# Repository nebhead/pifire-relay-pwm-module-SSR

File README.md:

# PiFire Solid State Relay (SSR) Module PCB (v1.0.1) KiCad Files

## What is this? 

This PCB is designed to support SSR relays for controlling incoming Power(L) to the Igniter and Auger.  This board also has circuitry to support a 12V PWM fan.  This board uses compact solid state relays that are able to handle high power. This is an alternative to using an off the shelf relay module which simplifies the wiring and even allows you to use the OEM harness.  

The design intent for this board was to make a DIY accessible PCB that can be more easily put together by the maker/enthusiast of almost any skill level.  Full size components are used in most cases and most (if not all) parts should be readily available to order online.  See the [Interactive BOM](#interactive-bom) for more details about the parts used and links to order.

### Important Notes

This PCB is intended to be used with the 4.0.x PCB design ([linked below](#links-to-the-pcbs-in-this-family-of-pifire-boards)) in conjunction with v1.8.x or later of the PiFire software.

The G3MB Relays and the PSMN MOSFET footprints have been left out of this release because they were sourced from SnapMagic (for free), but are not licensed for re-distribution.  If you plan to edit this board, you may need to source those files from SnapMagic directly and add them to this project.  

### What is PiFire? 

PiFire is a SBC based Pellet Smoker Controller.  More details can be found [here](https://nebhead.github.io/PiFire) or [at the GitHub repo](https://github.com/nebhead/pifire). 

## What's in this Repository?

### KiCad Project Files 
In this repository you will find the latest KiCad design files for the  PCB.  Simply load the project file (.kicad_pro) into the KiCad software and you should be able to edit as needed.  Or if you just want to get this board made, jump to the production section below.

### Interactive BOM

There is an interactive BOM located in the [/bom](bom/) folder which details the parts and provides some pin information as well.  Use this to gather the components you may need to build this board out and refer back to it for placement help.    

[BOM + Pin Info](https://nebhead.github.io/pifire-relay-pwm-module-SSR)

_This is a standalone HTML file that was autogenerated by the excellent plugin for KiCad. See the plugin here: [https://github.com/openscopeproject/InteractiveHtmlBom](https://github.com/openscopeproject/InteractiveHtmlBom)_

### PDF of the Schematic

Preview the schematic in PDF format here: [Schematic](schematic.pdf)

### PWM Fan Pinout

The PWM fan pinout is using a standard 4-pin fan connector.  It's recommended to source the headers with retaining clip to ensure that the fan doesn't easily come unplugged.  JST headers can be used as well. 

### JLCPCB Production Files

If you wish to get these PCBs made by JLCPCB, the production files are provided in the `/production` folder.  For convenience, the file `production.zip` can simply be uploaded to JLCPCB to make it super easy to order boards.

Drop the zip file onto the order page, wait for it to upload then simply continue to order the board.  Optionally, select different board color, PCB quantity, surface finish, etc.  Most of the default settings should be sufficient. 

### Links to the PCBs in this family of PiFire Boards

This PCB is part of a family of PCBs that can be used together to create  a full PiFire system.  Generally speaking you need the Main Module/Board, a Relay Control Board and a Probe Device board to have a basic PiFire system.  

**Main Module/Board** (required)
* [Main Board v4.0.x](https://github.com/nebhead/pifire-main-module-nopwr)

**Relay/Fan Control Boards** (choose one)
* [Mechanical Relay Module](https://github.com/nebhead/pifire-relay-module)
* [Solid State Relay Module](https://github.com/nebhead/pifire-relay-module-ssr)
* [Solid State Relay + PWM Fan Module](https://github.com/nebhead/pifire-relay-pwm-module-ssr) - Original Design
* [Solid State Relay + PWM Fan Module Alternate](https://github.com/nebhead/pifire-relay-pwm-module-ssr-alt) - Updated Design (Designed with help from @labmonkeyrat on Discord)

**Probe Device Board** (optional)
* [ADS Board](https://github.com/nebhead/pifire-ads-board) 

### 3D Printable Enclosures/Boxes 

With all of the 3D Prints for PiFire, a higher temperature filament such as PETG should be used.  PLA generally won't stand up to the temperatures that the components may be exposed to outdoors and near a hot smoker.  

#### Enclosure

Included here is an initial revision of the enclosure for this PCB.  The current models should be considered still in development and may have alignment challenges, etc. 

Except for the mounting wings, the majority of bolts to be used with this enclosure are M3. 

* STL: [Base](/printables/PiFire-v4-Relay-Base.stl)
* STL: [Lid](/printables/PiFire-v4-Relay-Lid.stl)
* OnShape: [Enclosure Original Models](https://cad.onshape.com/documents/03559f76f7adf190bf6f1259/w/7529cb0e4cd69db1a6a15202/e/07d5f9d46dc8f2b9e7dd655f?renderMode=0&uiState=66e11de950d7684b88999a0f)

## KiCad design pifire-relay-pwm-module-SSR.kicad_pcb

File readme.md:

# PiFire Solid State Relay (SSR) Module PCB (v1.0.1) KiCad Files

## What is this? 

This PCB is designed to support SSR relays for controlling incoming Power(L) to the Igniter and Auger.  This board also has circuitry to support a 12V PWM fan.  This board uses compact solid state relays that are able to handle high power. This is an alternative to using an off the shelf relay module which simplifies the wiring and even allows you to use the OEM harness.  

The design intent for this board was to make a DIY accessible PCB that can be more easily put together by the maker/enthusiast of almost any skill level.  Full size components are used in most cases and most (if not all) parts should be readily available to order online.  See the [Interactive BOM](#interactive-bom) for more details about the parts used and links to order.

### Important Notes

This PCB is intended to be used with the 4.0.x PCB design ([linked below](#links-to-the-pcbs-in-this-family-of-pifire-boards)) in conjunction with v1.8.x or later of the PiFire software.

The G3MB Relays and the PSMN MOSFET footprints have been left out of this release because they were sourced from SnapMagic (for free), but are not licensed for re-distribution.  If you plan to edit this board, you may need to source those files from SnapMagic directly and add them to this project.  

### What is PiFire? 

PiFire is a SBC based Pellet Smoker Controller.  More details can be found [here](https://nebhead.github.io/PiFire) or [at the GitHub repo](https://github.com/nebhead/pifire). 

## What's in this Repository?

### KiCad Project Files 
In this repository you will find the latest KiCad design files for the  PCB.  Simply load the project file (.kicad_pro) into the KiCad software and you should be able to edit as needed.  Or if you just want to get this board made, jump to the production section below.

### Interactive BOM

There is an interactive BOM located in the [/bom](bom/) folder which details the parts and provides some pin information as well.  Use this to gather the components you may need to build this board out and refer back to it for placement help.    

[BOM + Pin Info](https://nebhead.github.io/pifire-relay-module-SSR)

_This is a standalone HTML file that was autogenerated by the excellent plugin for KiCad. See the plugin here: [https://github.com/openscopeproject/InteractiveHtmlBom](https://github.com/openscopeproject/InteractiveHtmlBom)_

### PDF of the Schematic

Preview the schematic in PDF format here: [Schematic](schematic.pdf)

### JLCPCB Production Files

If you wish to get these PCBs made by JLCPCB, the production files are provided in the `/production` folder.  For convenience, the file `production.zip` can simply be uploaded to JLCPCB to make it super easy to order boards.

Drop the zip file onto the order page, wait for it to upload then simply continue to order the board.  Optionally, select different board color, PCB quantity, surface finish, etc.  Most of the default settings should be sufficient. 

### Links to the PCBs in this family of PiFire Boards

This PCB is part of a family of PCBs that can be used together to create  a full PiFire system.  Generally speaking you need the Main Module/Board, a Relay Control Board and a Probe Device board to have a basic PiFire system.  

**Main Module/Board** (required)
* [Main Board v4.0.x](https://github.com/nebhead/pifire-main-module-nopwr)

**Relay/Fan Control Boards** (choose one)
* [Mechanical Relay Module](https://github.com/nebhead/pifire-relay-module)
* [Solid State Relay Module](https://github.com/nebhead/pifire-relay-module-ssr)
* [Solid State Relay + PWM Fan Module](https://github.com/nebhead/pifire-relay-pwm-module-ssr)

**Probe Device Board** (optional)
* [ADS Board](https://github.com/nebhead/pifire-ads-board) 

### 3D Printable Enclosures/Boxes 

There aren't currently any 3D printable enclosures ready for this board.  When those are available, they will be linked here.

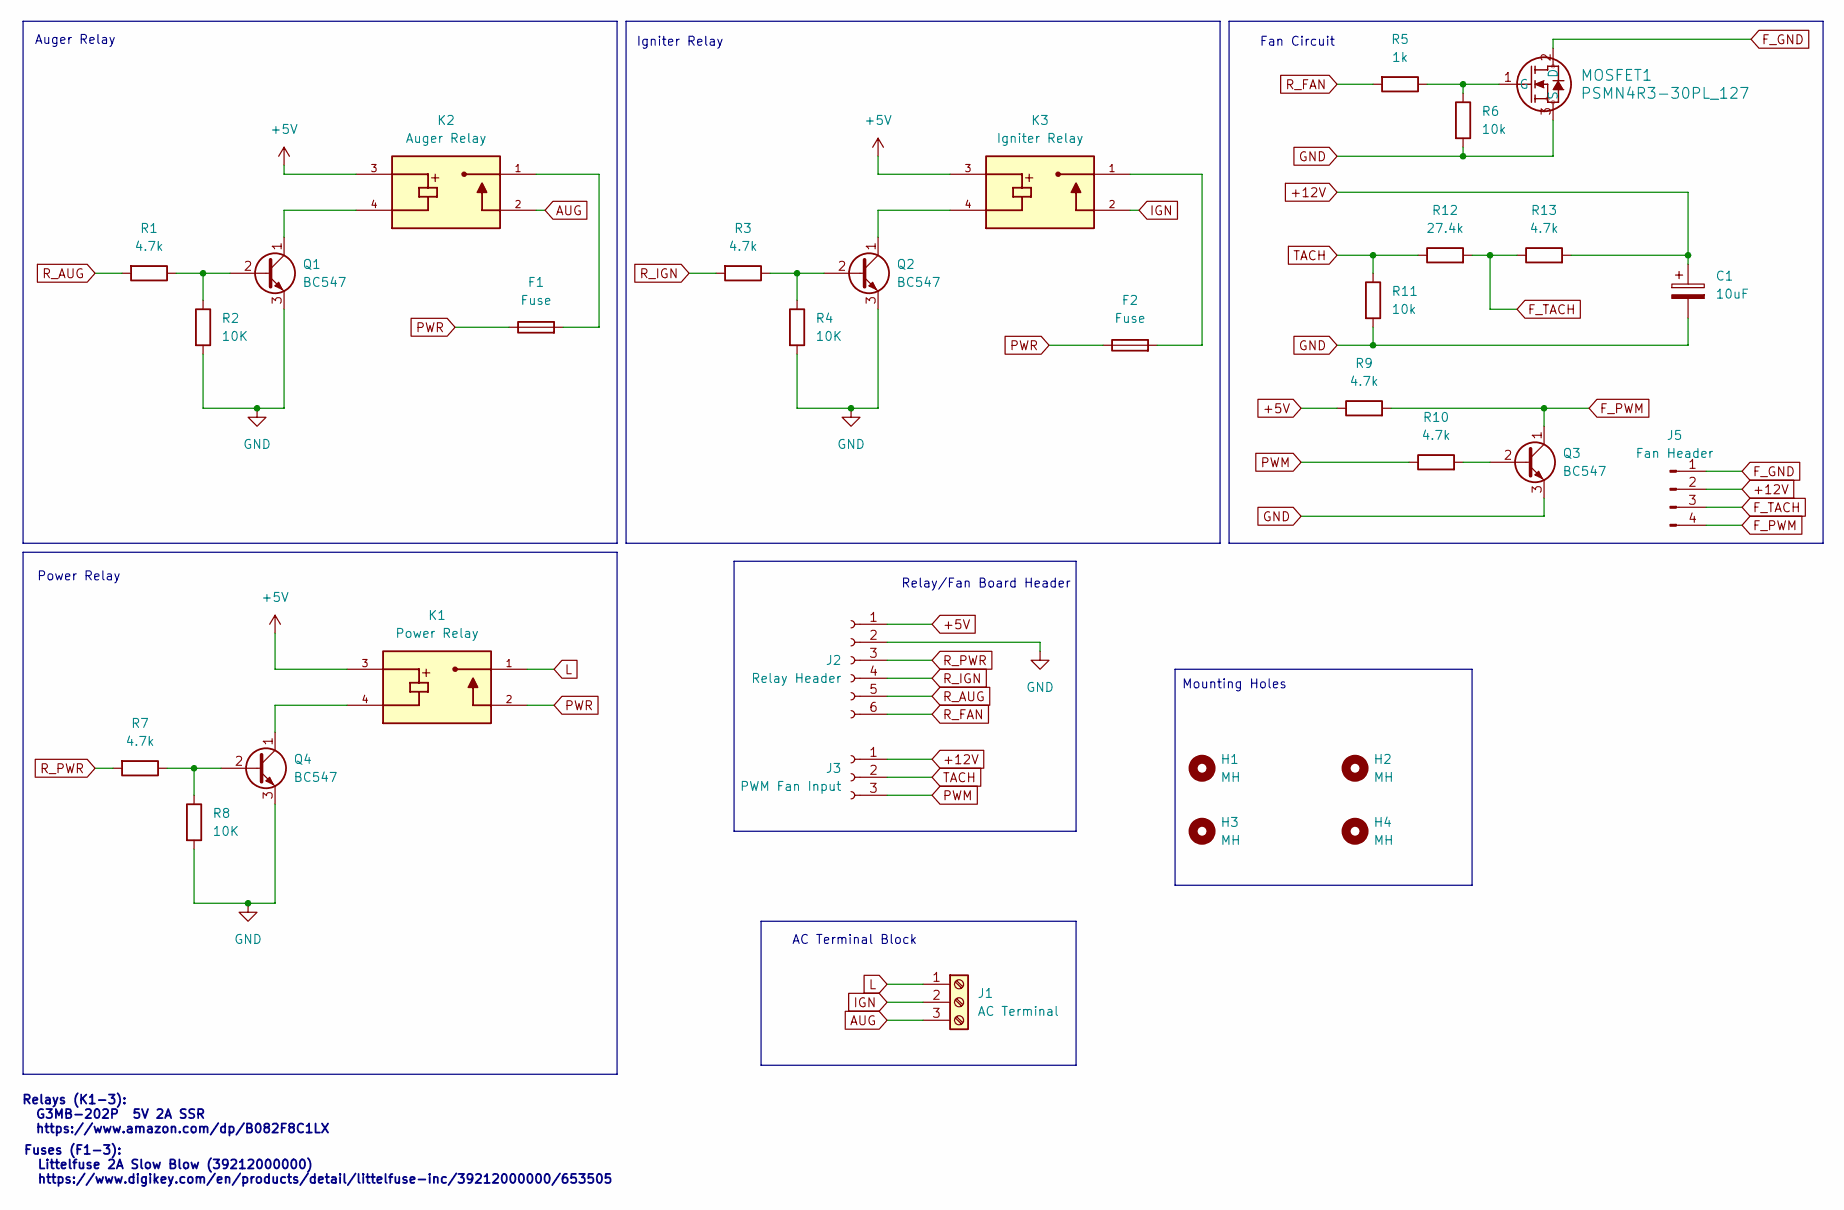
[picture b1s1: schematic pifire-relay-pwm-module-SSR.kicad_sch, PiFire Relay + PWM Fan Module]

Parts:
C1: 10uF; CP_Radial_D6.3mm_P2.50mm
F1, F2: Fuse; Fuse_Littelfuse_395Series
H1, H2, H3, H4: MH; MountingHole_3.2mm_M3
J1: AC Terminal; TerminalBlock_bornier-3_P5.08mm
J2: Relay Header; JST_XH_B6B-XH-A_1x06_P2.50mm_Vertical
J3: PWM Fan Input; JST_XH_B3B-XH-A_1x03_P2.50mm_Vertical
J5: Fan Header; FanPinHeader_1x04_P2.54mm_Vertical
K1: Power Relay; RELAY_G3MB-202PDC5; PARTREV J091-E1-1A
K2: Auger Relay; RELAY_G3MB-202PDC5; PARTREV J091-E1-1A
K3: Igniter Relay; RELAY_G3MB-202PDC5; PARTREV J091-E1-1A
MOSFET1: PSMN4R3-30PL_127; TO-220AB_SOT78_NEX
Q1, Q2, Q3, Q4: BC547; TO-92L_Inline
R1, R3, R7, R9, R10, R13: 4.7k; R_Axial_DIN0207_L6.3mm_D2.5mm_P7.62mm_Horizontal
R2, R4, R8: 10K; R_Axial_DIN0207_L6.3mm_D2.5mm_P7.62mm_Horizontal
R5: 1k; R_Axial_DIN0207_L6.3mm_D2.5mm_P7.62mm_Horizontal
R6, R11: 10k; R_Axial_DIN0207_L6.3mm_D2.5mm_P7.62mm_Horizontal
R12: 27.4k; R_Axial_DIN0207_L6.3mm_D2.5mm_P7.62mm_Horizontal

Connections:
+5V: J2.1, K1.3, K2.3, K3.3, R9.1
+12V: C1.1, J3.1, J5.2, R13.2
AUG: J1.3, K2.2
F_GND: J5.1, MOSFET1.2 (D)
F_PWM: J5.4, Q3.1 (C), R9.2
F_TACH: J5.3, R12.2, R13.1
GND: C1.2, J2.2, MOSFET1.3 (S), Q1.3 (E), Q2.3 (E), Q3.3 (E), Q4.3 (E), R2.2, R4.2, R6.2, R8.2, R11.2
IGN: J1.2, K3.2
L: J1.1, K1.1
unnamed: F1.2, K2.1
unnamed: F2.2, K3.1
unnamed: MOSFET1.1 (G), R5.1, R6.1
unnamed: Q1.2 (B), R1.1, R2.1
unnamed: K2.4, Q1.1 (C)
unnamed: Q2.2 (B), R3.1, R4.1
unnamed: K3.4, Q2.1 (C)
unnamed: Q3.2 (B), R10.2
unnamed: Q4.2 (B), R7.1, R8.1
unnamed: K1.4, Q4.1 (C)
PWM: J3.3, R10.1
PWR: F1.1, F2.1, K1.2
R_AUG: J2.5, R1.2
R_FAN: J2.6, R5.2
R_IGN: J2.4, R3.2
R_PWR: J2.3, R7.2
TACH: J3.2, R11.1, R12.1

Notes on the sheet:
Fan Circuit
Power Relay
Fuses (F1-3): Littelfuse 2A Slow Blow (39212000000) https://www.digikey.com/en/products/detail/littelfuse-inc/39212000000/653505
AC Terminal Block
Auger Relay
Relay/Fan Board Header
Relays (K1-3): G3MB-202P 5V 2A SSR https://www.amazon.com/dp/B082F8C1LX
Mounting Holes
Igniter Relay

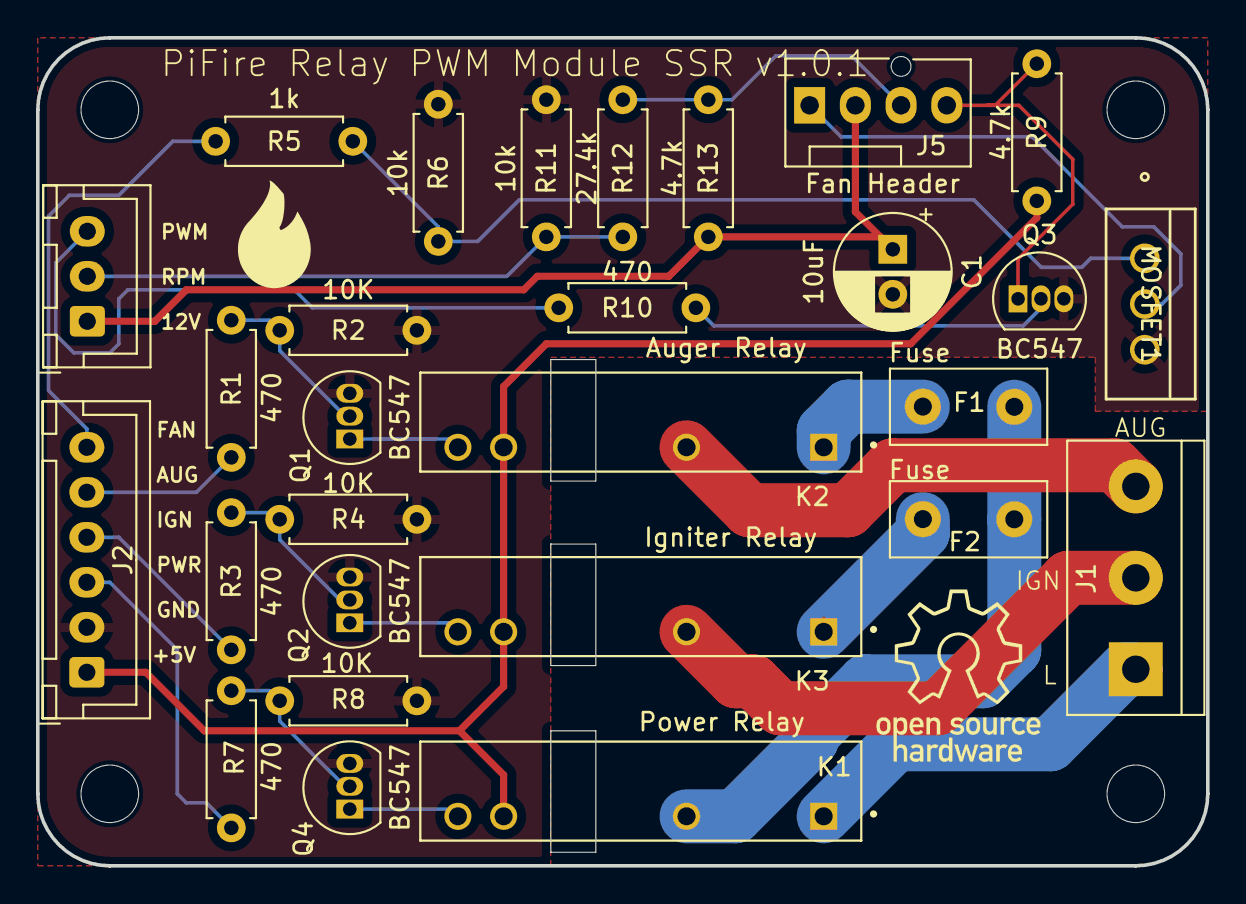
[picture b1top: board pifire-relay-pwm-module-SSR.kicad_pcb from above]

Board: 2 copper layers, 65.0 x 46.0 mm, 32 parts (0 on the bottom side), 26 nets.

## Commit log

2024-06-07 First Release
2024-06-07 Update link to BOM
2024-06-07 Rename BOM HTML
2024-09-07 Update README.md
    Add alternate PWM board.
2024-09-11 Added 3D Printables
2025-04-16 Updated with PWM Fan Pinout
2025-12-27 Updated Schematic
